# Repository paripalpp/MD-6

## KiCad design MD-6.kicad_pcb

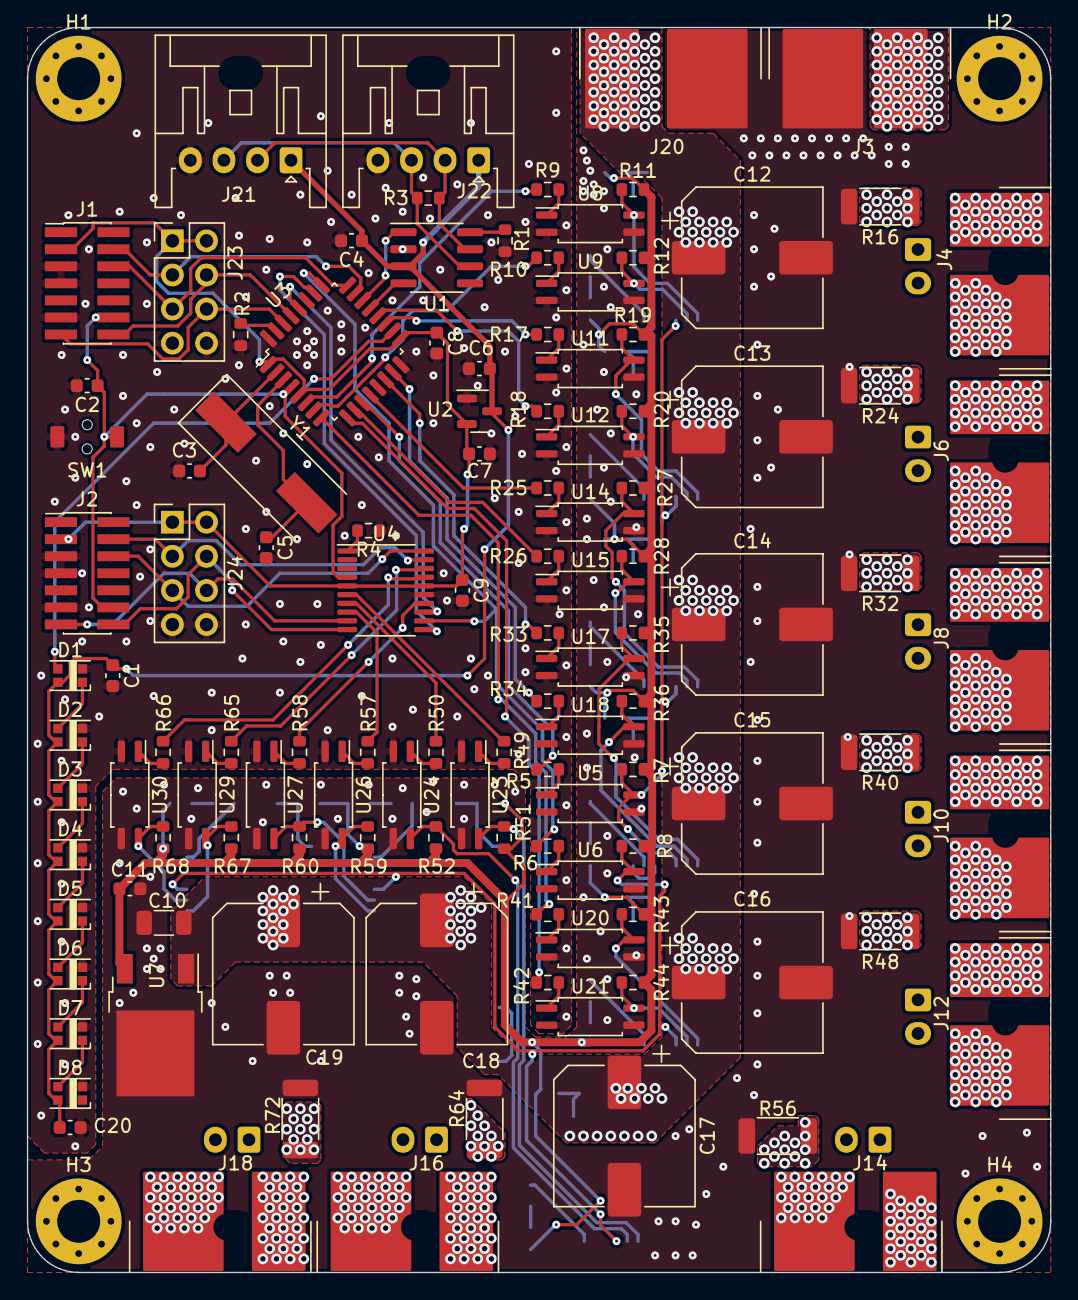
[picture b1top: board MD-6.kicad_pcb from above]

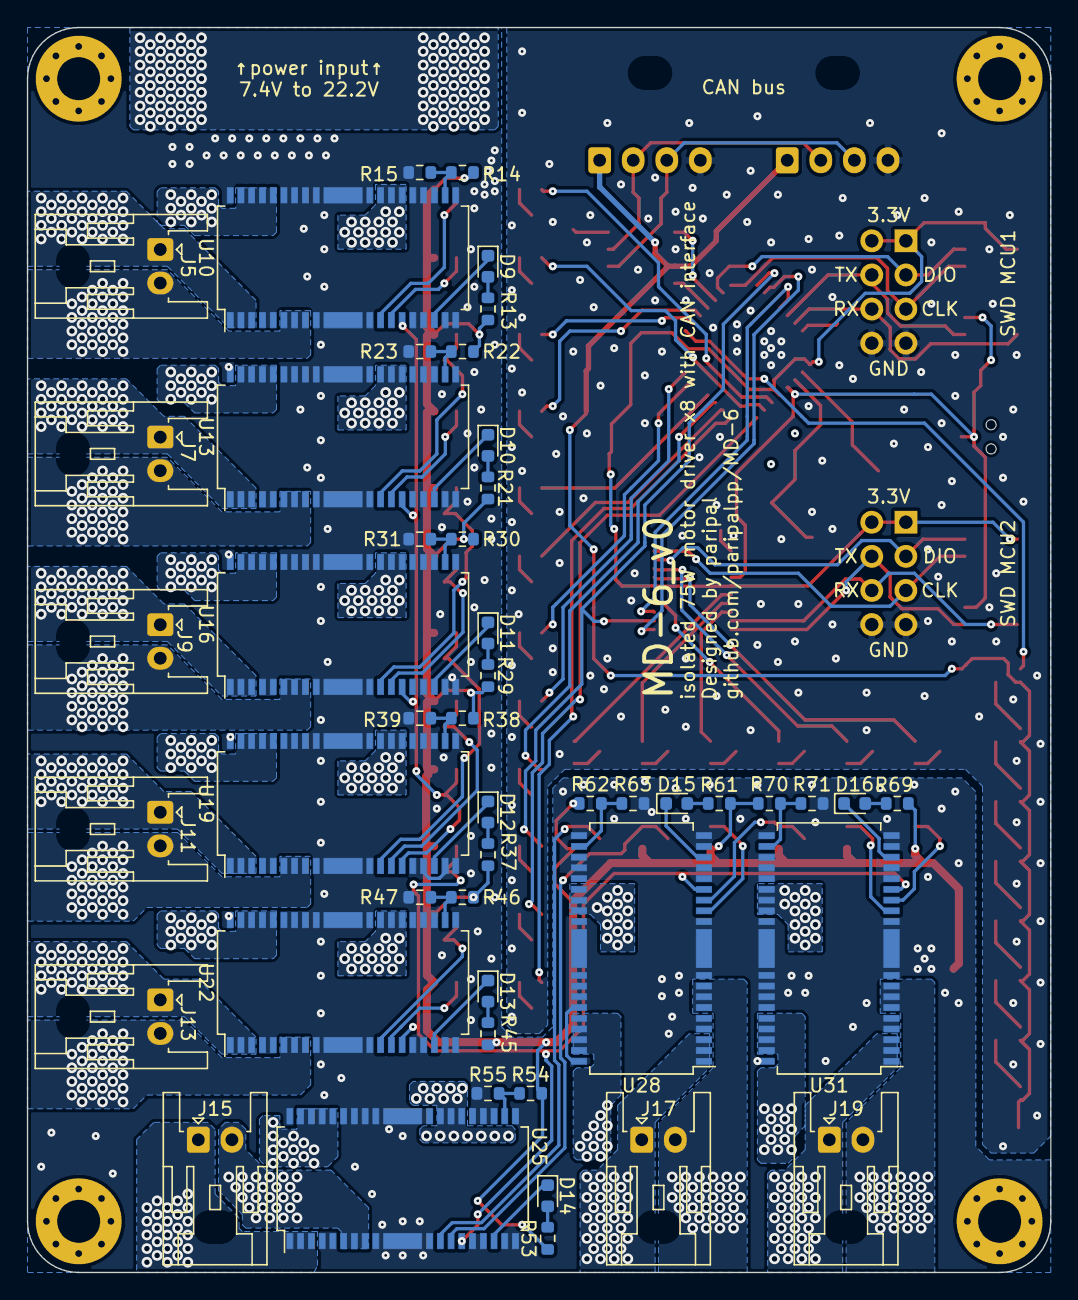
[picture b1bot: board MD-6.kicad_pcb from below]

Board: 2 copper layers, 76.2 x 92.7 mm, 169 parts (48 on the bottom side), 129 nets.

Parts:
C1, C6, C7, C8, C11, C20: 1uF; C_0603_1608Metric
C2, C4, C9: 0.1uF; C_0603_1608Metric
C3, C5: 22pF; C_0603_1608Metric
C10: 10uF; C_1206_3216Metric
C12, C13, C14, C15, C16, C17, C18, C19: C_Polarized; CP_Elec_10x10
D1, D2, D3, D4, D5, D6, D7, D8: WS2812C; LED_2020Metric_WS2812C_2.0x2.0mm_P1.0mm
D9, D10, D11, D12, D13, D14, D15, D16: LED; LED_0603_1608Metric
H1, H2, H3, H4: MountingHole; MountingHole_3.2mm_M3_Pad_Via
J1, J2: Conn_02x07_Odd_Even; PinHeader_2x07_P1.27mm_Vertical_SMD
J3: Conn_01x02_Male; T_connecter_male_horizontal
J4, J6, J8, J10, J12, J14, J16, J18, J20: Conn_01x02_Female; T_connecter_female_horizontal
J5, J7, J9, J11, J13, J15, J17, J19: Conn_01x02_Female; JST_XA_S02B-XASK-1_1x02_P2.50mm_Horizontal
J21, J22: Conn_01x04_Female; JST_XA_S04B-XASK-1_1x04_P2.50mm_Horizontal
J23, J24: Conn_02x04_Odd_Even; PinHeader_2x04_P2.54mm_Vertical
R1, R2, R4: 10kR; R_0603_1608Metric
R3: 120R; R_0603_1608Metric
R5, R6, R9, R10, R17, R18, R25, R26, R33, R34, R41, R42, R49, R50, R57, R58, R65, R66: 330; R_0603_1608Metric
R7, R8, R11, R12, R19, R20, R27, R28, R35, R36, R43, R44, R51, R52, R59, R60, R67, R68: 1k; R_0603_1608Metric
R13, R21, R29, R37, R45, R53, R61, R69: 10k; R_0603_1608Metric
R14, R15, R22, R23, R30, R31, R38, R39, R46, R47, R54, R55, R62, R63, R70, R71: R; R_0603_1608Metric
R16, R24, R32, R40, R48, R56, R64, R72: 0.1R 1W; R_2010_5025Metric
SW1: SW_Push; TVAF06-A020B-R
U1: MCP2551-I-SN; SOIC-8_3.9x4.9mm_P1.27mm
U2: MCP1792-3302H; SOT-23
U3: STM32F303K8Tx; LQFP-32_7x7mm_P0.8mm
U4: STM32L010F4P6; TSSOP-20_4.4x6.5mm_P0.65mm
U5, U6, U8, U9, U11, U12, U14, U15, U17, U18, U20, U21, U23, U24, U26, U27, U29, U30: TLP291; SOIC-4_4.55x2.6mm_P1.27mm
U7: L7805; TO-252-2
U10, U13, U16, U19, U22, U25, U28, U31: BD63130AFM; Rohm_HSOP-M36_7.5x18.5mm_P0.8mm
Y1: 16MHz; Crystal_SMD_HC49-SD

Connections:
+3V3: C7.1, C8.1, C9.1, J1.3, J2.3, J23.1, J23.2, J24.1, J24.2, U2.2 (VO), U3.1 (VDD), U3.5 (VDDA), U3.17 (VDD), U4.5 (VDDA), U4.16 (VDD)
+5V: C1.1, C4.1, C6.1, C20.1, D1.4 (VDD), D2.4 (VDD), D3.4 (VDD), D4.4 (VDD), D5.4 (VDD), D6.4 (VDD), D7.4 (VDD), D8.4 (VDD), J21.1, J22.1, U1.3 (VDD), U2.3 (VI)
+5VP: C11.1, R7.2, R8.2, R11.2, R12.2, R13.1, R14.1, R19.2, R20.2, R21.1, R22.1, R27.2, R28.2, R29.1, R30.1, R35.2, R36.2, R37.1, R38.1, R43.2, R44.2, R45.1, R46.1, R51.2, R52.2, R53.1, R54.1, R59.2, R60.2, R61.1, R62.1, R67.2, R68.2, R69.1, R70.1, U7.3 (OUT)
/ACTIVE1: R5.1, U3.11 (PA5)
/ACTIVE2: R6.1, U3.25 (PA15), U4.12 (PA6)
/BOOT0: R2.2, U3.31 (BOOT0)
/CANH: J21.2, J22.2, R3.1, U1.7 (CANH)
/CANL: J21.3, J22.3, R3.2, U1.6 (CANL)
/CAN_RX: U1.4 (RXD), U3.21 (PA11)
/CAN_TX: U1.1 (TXD), U3.22 (PA12)
/EN1: R7.1, U5.4, U10.13 (PS), U13.13 (PS), U16.13 (PS), U19.13 (PS)
/EN2: R8.1, U6.4, U22.13 (PS), U25.13 (PS), U28.13 (PS), U31.13 (PS)
/MC1_SWCLK: J1.6, J23.5, U3.24 (PA14)
/MC1_SWDIO: J1.4, J23.3, U3.23 (PA13)
/MC1_VCP_RX: J1.13, J23.6, U3.30 (PB7)
/MC1_VCP_TX: J1.14, J23.4, U3.29 (PB6)
/MC2_SWCLK: J2.6, J24.5, U4.20 (PA14)
/MC2_SWDIO: J2.4, J24.3, U4.19 (PA13)
/MC2_VCP_RX: J2.13, J24.6, U4.9 (PA3)
/MC2_VCP_TX: J2.14, J24.4, U4.10 (PA4)
/NRST: C2.1, J1.12, J2.12, SW1.2, U3.4 (NRST), U4.4 (NRST)
/NeoPixel: D1.3 (DIN), U3.18 (PA8)
/OSC_IN: C3.1, U3.2 (PF0), Y1.1
/OSC_OUT: C5.1, U3.3 (PF1), Y1.2
/SPI_dat: U3.28 (PB5), U4.13 (PA7)
/SPI_sck: U3.26 (PB3), U4.11 (PA5)
/T2C1_M11: R9.1, U3.6 (PA0)
/T2C1_M61: R49.1, U4.6 (PA0)
/T2C2_M12: R10.1, U3.7 (PA1)
/T2C2_M62: R50.1, U4.7 (PA1)
/T2C3_M21: R17.1, U3.19 (PA9)
/T2C3_M71: R57.1, U4.8 (PA2)
/T2C4_M22: R18.1, U3.20 (PA10)
/T2C4_M72: R58.1, U4.14 (PB1)
/T3C1_M31: R25.1, U3.12 (PA6)
/T3C2_M32: R26.1, U3.10 (PA4)
/T3C3_M41: R33.1, U3.14 (PB0)
/T3C4_M42: R34.1, U3.15 (PB1)
/T15C1_M51: R41.1, U3.8 (PA2)
/T15C2_M52: R42.1, U3.9 (PA3)
/T21C1_M81: R65.1, U4.18 (PA10)
/T21C2_M82: R66.1, U4.17 (PA9)
/driver1/IN1P: R11.1, U8.4, U10.11 (IN1)
/driver1/IN2P: R12.1, U9.4, U10.12 (IN2)
/driver1/OUT1: J4.1, J5.1, U10.1 (OUT1), U10.2 (OUT1), U10.3 (OUT1)
/driver1/OUT2: J4.2, J5.2, U10.6 (OUT2), U10.7 (OUT2), U10.8 (OUT2)
/driver2/IN1P: R19.1, U11.4, U13.11 (IN1)
/driver2/IN2P: R20.1, U12.4, U13.12 (IN2)
/driver2/OUT1: J6.1, J7.1, U13.1 (OUT1), U13.2 (OUT1), U13.3 (OUT1)
/driver2/OUT2: J6.2, J7.2, U13.6 (OUT2), U13.7 (OUT2), U13.8 (OUT2)
/driver3/IN1P: R27.1, U14.4, U16.11 (IN1)
/driver3/IN2P: R28.1, U15.4, U16.12 (IN2)
/driver3/OUT1: J8.1, J9.1, U16.1 (OUT1), U16.2 (OUT1), U16.3 (OUT1)
/driver3/OUT2: J8.2, J9.2, U16.6 (OUT2), U16.7 (OUT2), U16.8 (OUT2)
/driver4/IN1P: R35.1, U17.4, U19.11 (IN1)
/driver4/IN2P: R36.1, U18.4, U19.12 (IN2)
/driver4/OUT1: J10.1, J11.1, U19.1 (OUT1), U19.2 (OUT1), U19.3 (OUT1)
/driver4/OUT2: J10.2, J11.2, U19.6 (OUT2), U19.7 (OUT2), U19.8 (OUT2)
/driver5/IN1P: R43.1, U20.4, U22.11 (IN1)
/driver5/IN2P: R44.1, U21.4, U22.12 (IN2)
/driver5/OUT1: J12.1, J13.1, U22.1 (OUT1), U22.2 (OUT1), U22.3 (OUT1)
/driver5/OUT2: J12.2, J13.2, U22.6 (OUT2), U22.7 (OUT2), U22.8 (OUT2)
/driver6/IN1P: R51.1, U23.4, U25.11 (IN1)
/driver6/IN2P: R52.1, U24.4, U25.12 (IN2)
/driver6/OUT1: J14.1, J15.1, U25.1 (OUT1), U25.2 (OUT1), U25.3 (OUT1)
/driver6/OUT2: J14.2, J15.2, U25.6 (OUT2), U25.7 (OUT2), U25.8 (OUT2)
/driver7/IN1P: R59.1, U26.4, U28.11 (IN1)
/driver7/IN2P: R60.1, U27.4, U28.12 (IN2)
/driver7/OUT1: J16.1, J17.1, U28.1 (OUT1), U28.2 (OUT1), U28.3 (OUT1)
/driver7/OUT2: J16.2, J17.2, U28.6 (OUT2), U28.7 (OUT2), U28.8 (OUT2)
/driver8/IN1P: R67.1, U29.4, U31.11 (IN1)
/driver8/IN2P: R68.1, U30.4, U31.12 (IN2)
/driver8/OUT1: J18.1, J19.1, U31.1 (OUT1), U31.2 (OUT1), U31.3 (OUT1)
/driver8/OUT2: J18.2, J19.2, U31.6 (OUT2), U31.7 (OUT2), U31.8 (OUT2)
GND: C1.2, C2.2, C3.2, C4.2, C5.2, C6.2, C7.2, C8.2, C9.2, C20.2, D1.2 (VSS), D2.2 (VSS), D3.2 (VSS), D4.2 (VSS), D5.2 (VSS), D6.2 (VSS), D7.2 (VSS), D8.2 (VSS), J1.5, J1.7, J1.11, J2.5, J2.7, J2.11, J21.4, J22.4, J23.7, J23.8, J24.7, J24.8, R1.1, R2.1, R4.1, SW1.1, U1.2 (VSS), U2.1 (GND), U3.16 (VSS), U3.32 (VSS), U4.15 (VSS), U5.2, U6.2, U8.2, U9.2, U11.2, U12.2, U14.2, U15.2, U17.2, U18.2, U20.2, U21.2, U23.2, U24.2, U26.2, U27.2, U29.2, U30.2
GNDPWR: C10.2, C11.2, C12.2, C13.2, C14.2, C15.2, C16.2, C17.2, C18.2, C19.2, J3.2, J20.2, R15.2, R16.2, R23.2, R24.2, R31.2, R32.2, R39.2, R40.2, R47.2, R48.2, R55.2, R56.2, R63.2, R64.2, R71.2, R72.2, U5.3, U6.3, U7.2 (GND), U8.3, U9.3, U10.4 (NC), U10.5 (NC), U10.9 (NC), U10.10 (NC), U10.14 (NC), U10.15 (TEST), U10.17 (NC), U10.18 (TEST1), U10.19 (NC), U10.21 (NC), U10.22 (GRND), U10.23 (NC), U10.27 (NC), U10.28 (NC), U10.29 (GRND), U10.30 (NC), U10.31 (NC), U10.36 (NC), U10.37 (FIN), U10.38 (FIN), U11.3, U12.3, U13.4 (NC), U13.5 (NC), U13.9 (NC), U13.10 (NC), U13.14 (NC), U13.15 (TEST), U13.17 (NC), U13.18 (TEST1), U13.19 (NC), U13.21 (NC), U13.22 (GRND), U13.23 (NC), U13.27 (NC), U13.28 (NC), U13.29 (GRND), U13.30 (NC), U13.31 (NC), U13.36 (NC), U13.37 (FIN), U13.38 (FIN), U14.3, U15.3, U16.4 (NC), U16.5 (NC), U16.9 (NC), U16.10 (NC), U16.14 (NC), U16.15 (TEST), U16.17 (NC), U16.18 (TEST1), U16.19 (NC), U16.21 (NC), U16.22 (GRND), U16.23 (NC), U16.27 (NC), U16.28 (NC), U16.29 (GRND), U16.30 (NC), U16.31 (NC), U16.36 (NC), U16.37 (FIN), U16.38 (FIN), U17.3, U18.3, U19.4 (NC), U19.5 (NC), U19.9 (NC), U19.10 (NC), U19.14 (NC), U19.15 (TEST), U19.17 (NC), U19.18 (TEST1), U19.19 (NC), U19.21 (NC), U19.22 (GRND), U19.23 (NC), U19.27 (NC), U19.28 (NC), U19.29 (GRND), U19.30 (NC), U19.31 (NC), U19.36 (NC), U19.37 (FIN), U19.38 (FIN), U20.3, U21.3, U22.4 (NC), U22.5 (NC), U22.9 (NC), U22.10 (NC), U22.14 (NC), U22.15 (TEST), U22.17 (NC), U22.18 (TEST1), U22.19 (NC), U22.21 (NC), U22.22 (GRND), U22.23 (NC), U22.27 (NC), U22.28 (NC), U22.29 (GRND), U22.30 (NC), U22.31 (NC), U22.36 (NC), U22.37 (FIN), U22.38 (FIN), U23.3, U24.3, U25.4 (NC), U25.5 (NC), U25.9 (NC), U25.10 (NC), U25.14 (NC), U25.15 (TEST), U25.17 (NC), U25.18 (TEST1), U25.19 (NC), U25.21 (NC), U25.22 (GRND), U25.23 (NC), U25.27 (NC), U25.28 (NC), U25.29 (GRND), U25.30 (NC), U25.31 (NC), U25.36 (NC), U25.37 (FIN), U25.38 (FIN), U26.3, U27.3, U28.4 (NC), U28.5 (NC), U28.9 (NC), U28.10 (NC), U28.14 (NC), U28.15 (TEST), U28.17 (NC), U28.18 (TEST1), U28.19 (NC), U28.21 (NC), U28.22 (GRND), U28.23 (NC), U28.27 (NC), U28.28 (NC), U28.29 (GRND), U28.30 (NC), U28.31 (NC), U28.36 (NC), U28.37 (FIN), U28.38 (FIN), U29.3, U30.3, U31.4 (NC), U31.5 (NC), U31.9 (NC), U31.10 (NC), U31.14 (NC), U31.15 (TEST), U31.17 (NC), U31.18 (TEST1), U31.19 (NC), U31.21 (NC), U31.22 (GRND), U31.23 (NC), U31.27 (NC), U31.28 (NC), U31.29 (GRND), U31.30 (NC), U31.31 (NC), U31.36 (NC), U31.37 (FIN), U31.38 (FIN)
unnamed: D1.1 (DOUT), D2.3 (DIN)
unnamed: D2.1 (DOUT), D3.3 (DIN)
unnamed: D3.1 (DOUT), D4.3 (DIN)
unnamed: D4.1 (DOUT), D5.3 (DIN)
unnamed: D6.1 (DOUT), D7.3 (DIN)
unnamed: D5.1 (DOUT), D6.3 (DIN)
unnamed: D7.1 (DOUT), D8.3 (DIN)
unnamed: D9.1 (K), U10.16 (FAILA)
unnamed: D9.2 (A), R13.2
unnamed: D10.1 (K), U13.16 (FAILA)
unnamed: D10.2 (A), R21.2
unnamed: D11.1 (K), U16.16 (FAILA)
unnamed: D11.2 (A), R29.2
unnamed: D12.1 (K), U19.16 (FAILA)
unnamed: D12.2 (A), R37.2
unnamed: D13.1 (K), U22.16 (FAILA)
unnamed: D13.2 (A), R45.2
unnamed: D14.1 (K), U25.16 (FAILA)
unnamed: D14.2 (A), R53.2
unnamed: D15.1 (K), U28.16 (FAILA)
unnamed: D15.2 (A), R61.2
unnamed: D16.1 (K), U31.16 (FAILA)
unnamed: D16.2 (A), R69.2
unnamed: R1.2, U1.8 (Rs)
unnamed: R4.2, U4.1 (PB9)
unnamed: R5.2, U5.1
unnamed: R6.2, U6.1
unnamed: R9.2, U8.1
unnamed: R10.2, U9.1
unnamed: R14.2, R15.1, U10.20 (VREF)
unnamed: R17.2, U11.1
unnamed: R18.2, U12.1
unnamed: R22.2, R23.1, U13.20 (VREF)
unnamed: R25.2, U14.1
unnamed: R26.2, U15.1
unnamed: R30.2, R31.1, U16.20 (VREF)
unnamed: R33.2, U17.1
unnamed: R34.2, U18.1
unnamed: R38.2, R39.1, U19.20 (VREF)
unnamed: R41.2, U20.1
unnamed: R42.2, U21.1
unnamed: R46.2, R47.1, U22.20 (VREF)
unnamed: R49.2, U23.1
unnamed: R50.2, U24.1
unnamed: R54.2, R55.1, U25.20 (VREF)
unnamed: R57.2, U26.1
unnamed: R58.2, U27.1
unnamed: R62.2, R63.1, U28.20 (VREF)
unnamed: R65.2, U29.1
unnamed: R66.2, U30.1
unnamed: R70.2, R71.1, U31.20 (VREF)
RNF: R16.1, R24.1, R32.1, R40.1, R48.1, R56.1, R64.1, R72.1, U10.32 (RNFS), U10.33 (RNF), U10.34 (RNF), U10.35 (RNF), U13.32 (RNFS), U13.33 (RNF), U13.34 (RNF), U13.35 (RNF), U16.32 (RNFS), U16.33 (RNF), U16.34 (RNF), U16.35 (RNF), U19.32 (RNFS), U19.33 (RNF), U19.34 (RNF), U19.35 (RNF), U22.32 (RNFS), U22.33 (RNF), U22.34 (RNF), U22.35 (RNF), U25.32 (RNFS), U25.33 (RNF), U25.34 (RNF), U25.35 (RNF), U28.32 (RNFS), U28.33 (RNF), U28.34 (RNF), U28.35 (RNF), U31.32 (RNFS), U31.33 (RNF), U31.34 (RNF), U31.35 (RNF)
VCC: C10.1, C12.1, C13.1, C14.1, C15.1, C16.1, C17.1, C18.1, C19.1, J3.1, J20.1, U7.1 (IN), U10.24 (VCC), U10.25 (VCC), U10.26 (VCC), U13.24 (VCC), U13.25 (VCC), U13.26 (VCC), U16.24 (VCC), U16.25 (VCC), U16.26 (VCC), U19.24 (VCC), U19.25 (VCC), U19.26 (VCC), U22.24 (VCC), U22.25 (VCC), U22.26 (VCC), U25.24 (VCC), U25.25 (VCC), U25.26 (VCC), U28.24 (VCC), U28.25 (VCC), U28.26 (VCC), U31.24 (VCC), U31.25 (VCC), U31.26 (VCC)

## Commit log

2022-07-19 gitignore update
2022-07-24 some
2022-07-25 v0 done
2022-07-25 pdf and png plot
